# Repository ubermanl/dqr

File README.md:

# DqR Domo
DqR Domo permite el control, monitoreo y administración remota de su red eléctrica mediante cualquier dispositivo móvil o computadora personal.

Mediante DqR Domo podrá integrar y administrar de manera unificada todos sus dispositivos eléctricos, como luces, enchufes, portones, motores, etc., cualquiera sea su marca. La programación de tareas y la activación inteligente de dispositivos, junto con los reportes de consumo brindan toda la información que usted necesita para realizar un consumo más eficiente.

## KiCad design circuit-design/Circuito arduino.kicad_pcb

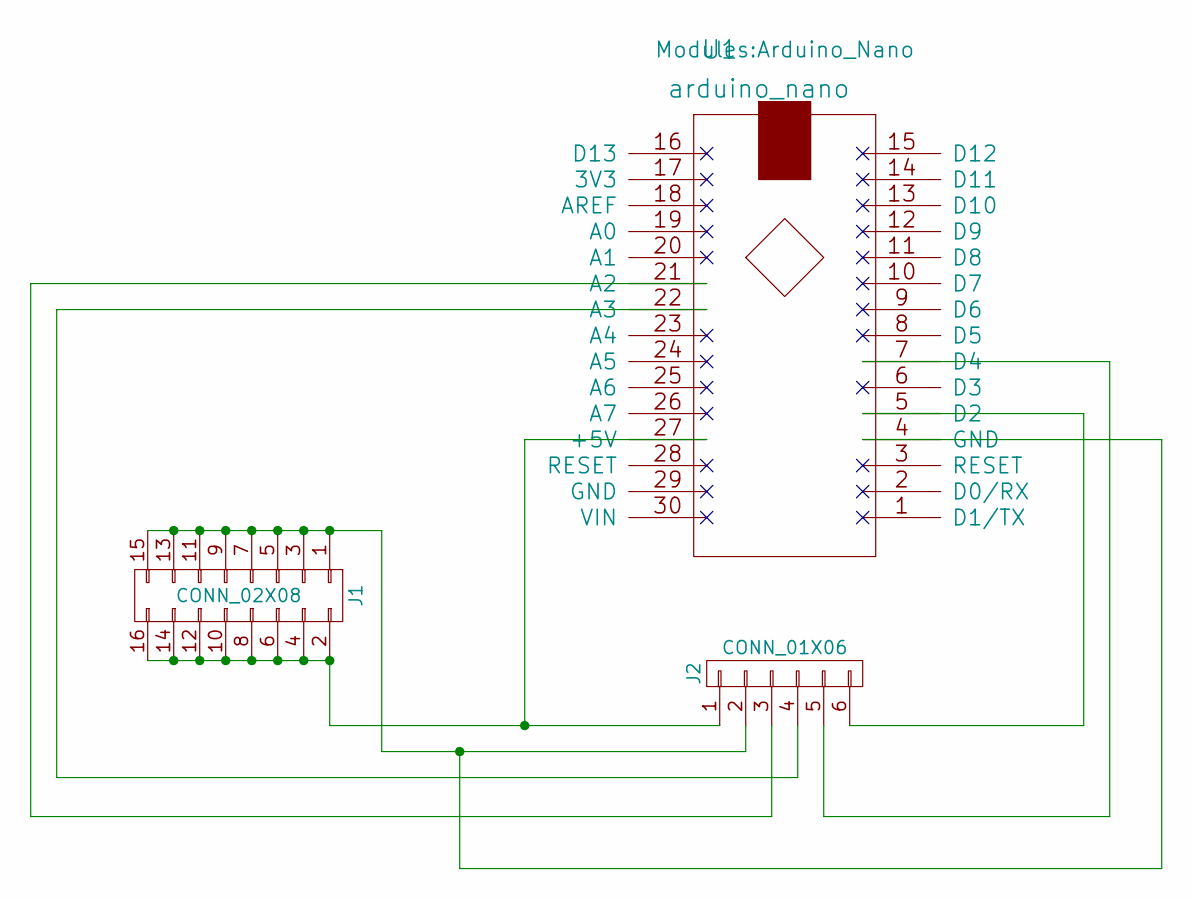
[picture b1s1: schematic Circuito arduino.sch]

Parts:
J1: CONN_02X08; Socket_Strip_Straight_2x08_Pitch2.54mm
J2: CONN_01X06; Pin_Header_Straight_1x06_Pitch2.54mm
U1: arduino_nano; Arduino_Nano

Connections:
unnamed: J1.1, J1.3, J1.5, J1.7, J1.9, J1.11, J1.13, J1.15, J2.2, U1.4 (GND)
unnamed: J1.2, J1.4, J1.6, J1.8, J1.10, J1.12, J1.14, J1.16, J2.1, U1.27 (+5V)
unnamed: J2.3, U1.21 (A2)
unnamed: J2.4, U1.22 (A3)
unnamed: J2.5, U1.7 (D4)
unnamed: J2.6, U1.5 (D2)

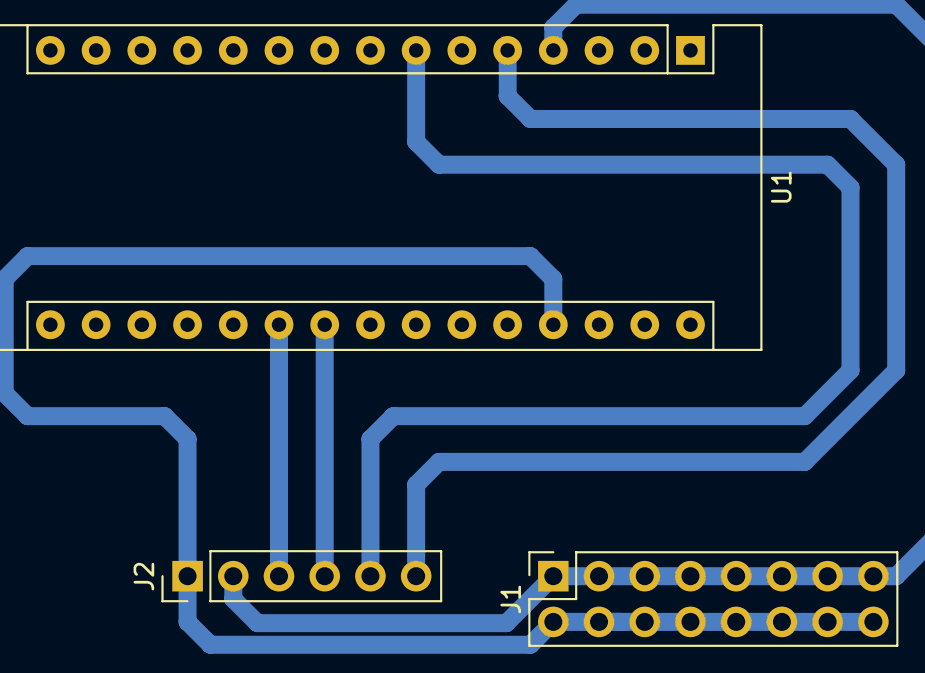
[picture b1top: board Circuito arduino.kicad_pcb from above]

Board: 2 copper layers, 3 parts (0 on the bottom side), 6 nets.

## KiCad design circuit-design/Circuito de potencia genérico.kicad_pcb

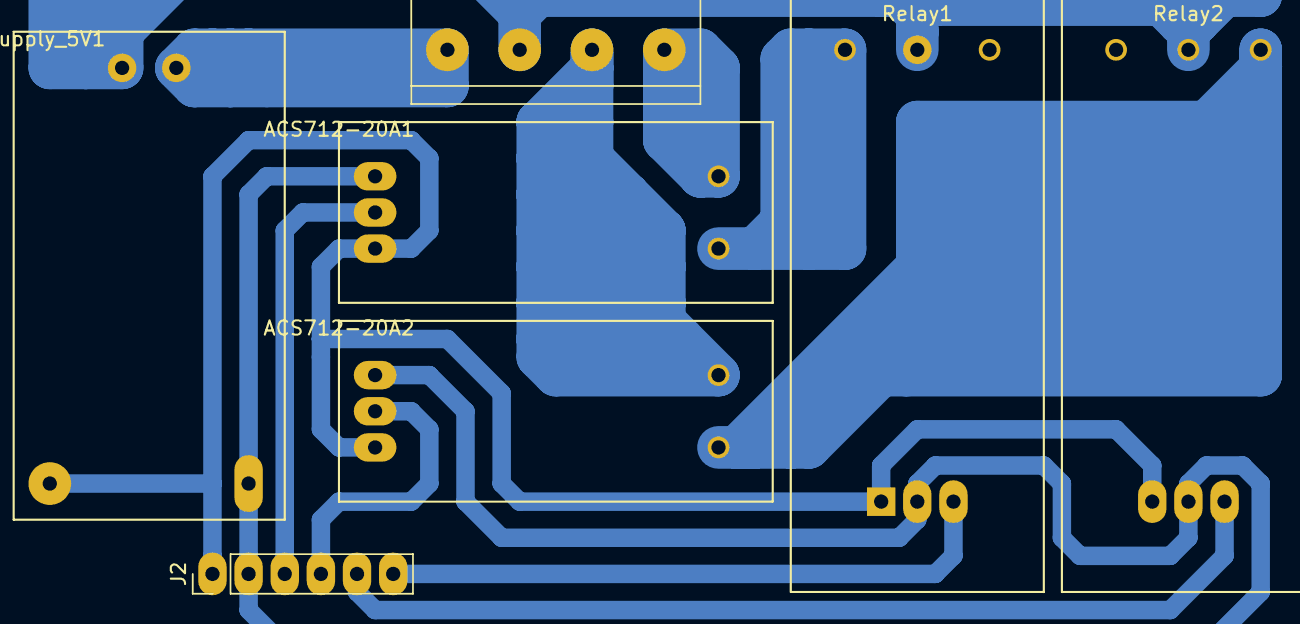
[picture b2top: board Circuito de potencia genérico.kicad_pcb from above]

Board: 2 copper layers, 7 parts (0 on the bottom side), 12 nets.

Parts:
ACS712-20A1, ACS712-20A2: ACS712-20A; ACS712
J1: Screw_Terminal_1x04; bornier4
J2: CONN_01X06; Pin_Header_Straight_1x06_Pitch2.54mm
PowerSupply_5V1: PowerSupply_5V; PowerSupply5V
Relay1, Relay2: Relay

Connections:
unnamed: ACS712-20A1.1, ACS712-20A2.1, J2.2, PowerSupply_5V1.4, Relay1.5, Relay2.5
unnamed: ACS712-20A1.2, J2.3
unnamed: ACS712-20A1.3, ACS712-20A2.3, J2.1, PowerSupply_5V1.3, Relay1.4, Relay2.4
unnamed: ACS712-20A1.4, J1.4
unnamed: ACS712-20A1.5, Relay1.2
unnamed: ACS712-20A2.2, J2.4
unnamed: ACS712-20A2.4, J1.3
unnamed: ACS712-20A2.5, Relay2.3
unnamed: J1.1, PowerSupply_5V1.2
unnamed: J1.2, PowerSupply_5V1.1, Relay1.1, Relay2.1
unnamed: J2.5, Relay2.6
unnamed: J2.6, Relay1.6

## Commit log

2017-04-02 Archivos iniciales para la prueba del dataset de UCI
2017-04-08 Nuevo ejemplo de RNA en un monoambiente y monousuario
2017-04-09 Incluyendo script para generar dataset y script para correr la RNA por cli
2017-04-13 Se reemplazó hora y minuto por minuto relativo del día
2017-04-17 ratio-console web
2017-04-17 gitignore
2017-04-17 fix database.yml
2017-04-17 Rename README.rdoc to README.md
2017-04-24 Nuevo servicio que corre la RNA y escucha consultas por medio de una API
2017-04-24 Nuevo doc en formato md
2017-04-24 Borrando doc mal formateado
2017-04-26 Ordenando los archivos
2017-04-27 Readme de RNA
2017-04-30 Actualizando para que todo use minutos relativos
2017-04-30 Actualización del README
2017-04-30 Más readme
2017-04-30 Typo
2017-05-03 Archivo de texto con versiones de módulos de pip
2017-05-16 Agregado de Arduino Lux
2017-05-22 Prueba del sensor ACS712 con suma de cuadrados
2017-05-25 random changes
2017-05-25 Agregada estabilizacion inicial del ACS712
2017-05-28 Actualizado completamente para poner los distintos tipos de dispositivo. Se agrego la cuenta para pasar de steps a Ampere.
2017-05-28 Se incluye lectura del sensor de luminosidad y su librería. Se reorganizaron los archivos.
2017-06-05 Funciones para los distintos sensores
2017-06-05 Empezando la definición de la librería DqR
2017-06-05 Mas modificaciones al prototipo de libreria
2017-06-05 sensor sonido en funcion
2017-06-05 Lux: se incorpora mensajes serial
2017-06-07 diseño modelo DB
2017-06-07 Migrado todo el código a clases
2017-06-09 Arreglada la cuenta de consumo AC
2017-06-12 Agregado de Interrupt por hw para switch touch
2017-06-12 Pruebas con FSM
2017-06-12 Agregado de lib FSM
2017-06-25 Versión inicial con el formato de clases device-module-sensor
2017-06-25 Cambios menores en los constructores
2017-06-26 Saqué "public" de la llamada de las clases heredadas
2017-06-26 reorganización del contenido
2017-06-26 dqr device sensor constructor
2017-06-26 rake task
2017-06-27 a better sample database config
2017-06-27 Se modifico la función addModules()
2017-06-29 Actualizaciones de hoy
2017-07-02 Actualización del ejemplo de clasificación para que tome al pir como una señal digital (0 y 1) en vez de continua.
2017-07-02 Nuevo ejemplo con regresión
2017-07-02 Actualizaciones varias
2017-07-02 Eliminado un checkpoint de jupyter-notebook
2017-07-04 Cambios de la sesión del lunes 3 de Julio
2017-07-08 # Agregado de librerías de comunicación RF24* de arduino # Ejemplos de arduino de FSM y RF24 # Implementacion inicial del Dispositivo (arduino/ejemplos/device-main)
2017-07-08 Correccion log estado 4 de prueba inicial device-main
2017-07-08 refactorizacion
2017-07-08 Creando la función getModuleStatus
2017-07-08 Se cambió getModuleStatus para que devuelva puntero a module_t
2017-07-10 # Cambios en pruebas de arduino main device # Agregado de pruebas de comunicacion con estructuras de datos para payload tipo I
2017-07-11 # Cambios en estructuras de datos de payload I
2017-07-12 Starbucks commit
2017-07-13 Starbucks session 2
2017-07-13 Cambio de low por high y viceversa
2017-07-13 Starbucks session #3
2017-07-14 # Cambios en dqr-device: - Agregado de sensores con punteros - Setup de device mediante struct constante en config - Modificaciones varias
2017-07-16 # Integración de dqr-device con FSM y RF24 # Versión inicial con envío de Informes de estado al Ratio completa. # Notificación al Ratio según parámetro de todos los módulos y sensores configurados. #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
2017-07-18 # Agregado de control de overflow del valor acumulado para el sensado
2017-07-26 # Versión inicial del módulo de comunicaciones del Ratio: ratioComm # Cambios en la instanciación de sensores, se elimina el id y se pasa a usar el type_id
2017-08-16 Agrego los archivos de diseño de circuito hechos con KiCad
2017-08-23 Archivos kicad de placa power
2017-08-30 fixes consola
2017-08-30 idea files
2017-09-05 nueva version de consola ratio
2017-09-05 Ratio SQL Dump
    Para poder crear la DB sin la App momentaneamente
2017-09-06 archivos omitidos
2017-09-06 # Cambios en la identificacion de modulos. El mod_id se autogenera
2017-09-06 Update README.md
    Actualiza las versiones de rails y ruby
2017-09-07 # Version inicial de modulo de comunicacion completo del Ratio
2017-09-10 Se agrega timestamp en LOG2
2017-09-10 Función antirebote en la captura del touch
2017-09-10 Faltaba poner timestamp en LOG
2017-09-10 Cambié el estado por default de LUX, para que no se prenda la luz cuando se inicializa el dispositivo
2017-09-10 Circuito de potencia genérico - v1.0
2017-09-10 Circuito Arduino Nano
2017-09-11 arreglos ratio communication
2017-09-11 arreglos en la compilacion via makefile en ratio communication
2017-09-11 Se agregan la comunicacion arduino-rpi para los mensajes S y A
2017-09-11 correcciones ratio-comm
2017-09-11 correccion en ratio-comm
2017-09-11 arreglos de version de scrypt y authlogic en gemfile
2017-09-11 agregado de retry de envios de mensajes a la mesh
2017-09-11 correcciones en max retries de envios
2017-09-11 correccion en el retry de envios de mensajes
2017-09-11 correcciones en la captura de sensado infinito.
2017-09-11 modificado retries desde el cliente
2017-09-12 Se movió el log de botón apretado dentro del comparador de tiempo
2017-09-13 correccion a la BOLUDEZ que hice en dqrMaster...
2017-09-13 correccion final del infinite en dqlMaster
2017-09-13 correccion de medicion de ACS en arduino
2017-09-13 Se cambio el estado por default de LUX
2017-09-14 correccion en el touch event del arduino para evitar bouncing y presiones minimas
2017-09-18 Cambios y correcciones en la logica de estados de los modulos.
2017-09-18 se agrega operacion con override al accionamiento remoto via ratio
2017-09-25 Added control of oldStatus on Lux to attempt control the errors detected during testing
2017-09-26 Added code to disable buffered output on stdout and stderr so that it's more service friendly
2017-09-27 Se crearon archivos de sistema para manejar los servicios relacionados con dqr, por ahora solo dqrMaster.
2017-09-27 new console status
2017-09-27 log perform
2017-09-27 fix activate deactivate
2017-09-27 fix send
2017-10-04 ajax toggles, new graphs
2017-10-04 fix toggle button
2017-10-04 fsm status override always
2017-10-12 devices, graficos, responsive
2017-10-17 github #4, #5
2017-10-17 timestamps correction to UTC
2017-10-17 autorefresh
2017-10-18 # Agregado de ejemplo de sensor de temperatura
2017-10-19 fixes
2017-10-20 generate lux task@
2017-10-21 Agregado de sensor de temperatura y estructura de templates para arduino
2017-10-22 Added systemd startup scripts for ratioConsole and moved all OS files to own directory
2017-10-22 Updated ratioConsole dependency
2017-10-22 Adding files to load firewall on boot and save on reboot/shutdwon
2017-10-22 Adding syslog file for ratioConsole, and other minor tweaks
2017-10-23 Correcicon include de DHT en arduino
2017-10-23 graph units added, console preferences
2017-10-23 rake task for unit update
2017-10-23 lux unit replaced
2017-10-23 fix potentia units
2017-10-23 ui face lift
2017-10-24 Updating service dependencies so that they start in the appropriate order (there were sql unavailable errors)
2017-10-24 Agregado de desactivacion de Omni en Arduino. Se vuelve atras el maximo de sensores a 5.
2017-10-25 Se cambiaron los permisos por default de dqrSender al ser instalado, para que el usuario pi (rails) pueda ejecutarlo.
2017-10-30 Agregada la generación de dataset para todo el año 2017.
2017-10-30 Se incluye función para sensar sonido en dBs, y se modificó el sensado de temperatura para truncar después del primer decimal
2017-10-30 Correcciones menores en los comentarios
2017-10-30 schedules
2017-10-30 Agregado consumo de luz al dataset simulado.
2017-10-31 scheduled tasks
2017-10-31 rake task disabled
2017-11-01 Agregada simulación de consumo de la heladera
2017-11-01 Agregado de carga de dataset en la base de datos
2017-11-01 timeline
2017-11-02 Updated Formula to calculate dBs and set new reference values
2017-11-03 Se agrega luminosidad medida por el lux
2017-11-03 Corrección en generador de dataset y agregado de pruebas de Classifier2 con variables modificadas
2017-11-03 Agregada prueba de nuevas variables del classifier2
2017-11-03 Agregado de nuevo modelo para predecir cambios de estado del lux.
2017-11-03 Correcciones en modelos de Classifier2
2017-11-03 Se elimina el dataset del git ya que puede generarse a demanda.
2017-11-04 cambio minimo al generador
2017-11-06 scheduler phase 1
2017-11-08 Added rnaEngine service
2017-11-08 pinned devices, discovery, device names
2017-11-08 Cleanup and and gitignore for the jupyter notebook checkpoints
2017-11-09 print last sensed value
2017-11-10 Carga de simulación en tablas device_events y device_event_sensors en la base de datos de DWH.
2017-11-10 device event sensors index
2017-11-11 Modificaciones menores para Python 3
2017-11-11 Borrado de checkpoints
2017-11-12 Ejemplo basado en LSTM
2017-11-12 Modificaciones menores
2017-11-14 Agregado ETL para pasar de TRX a DWH y predicción de consumo por módulo.
2017-11-14 Completada la carga en DWH en el ETL de aed_bi
2017-11-15 schedules preview, fixes github#74 schedule deletion
2017-11-15 schedules include attribute
2017-11-15 wait message for all ajax
2017-11-15 schedules bug out of sync
2017-11-15 Ya ni me acuerdo que agregué acá
2017-11-16 statistics on dashboard
2017-11-16 Agregado de variable en classifier2
2017-11-16 Nuevos ejemplos Classifier y Classifier LSTM con normalización
2017-11-18 Added multithreading to rnaEngine
2017-11-19 Cambio de librería DHT para el sensor de temperatura.
2017-11-19 fixes schedule status not reflexed, dqrSender failed message
2017-11-19 Added method to check if a give module has a model trained
2017-11-19 Added method to check if a give module has a trained model
2017-11-19 Deleting old file not longer in use
2017-11-19 swagger endpoint class
2017-11-19 protection against user entry
2017-11-20 Arreglado el comportamiento ante módulos invalidos o inexistentes
2017-11-20 user experience unified, login enabled
2017-11-20 user password change
2017-11-20 Corrección de bug de sensado de dispositivos no Omni en arduino
2017-11-20 fixes status transition
2017-11-20 fixes status output
2017-11-20 Fixed state training model
2017-11-20 graphics with fixed scale
2017-11-20 scheduler enabled
2017-11-20 Added default view of rnaEngine on root to display available methods
2017-11-21 fixes schedules
2017-11-22 scheduler enabled/disabled
2017-11-22 previous status check on schedule stop
2017-11-22 previous state fixed
2017-11-22 check schedule module multiple inclusion
2017-11-22 positive inclusion message
2017-11-22 fixed selecting schedule outside visible area
2017-11-22 Primera version del dashboard y agregado de procesos para Base de Datos.
2017-11-22 Adding more methods to the rnaEngine API portal
2017-11-22 name uniqueness
2017-11-22 redirect to detect device
2017-11-22 longitud nombre ambiente
2017-11-22 max name length 30 for all
2017-11-24 Version 1.1 del dashboard
2017-11-26 RBAC simple
2017-11-26 web page title
2017-11-28 fixes users, enable schedules again
2017-11-29 github #93
2017-11-29 fixes security issue on devices
2017-11-29 reenable scheduler
2017-11-29 sensor types and graph scale
2017-11-29 restrict type id change on sensor
2017-11-29 redirect to sensor_types on delete rejected
2017-12-07 Enabled schedules
2017-12-11 Added template for devices with single potentia module
2017-12-11 Added initial readme
2017-12-11 Minor modification to readme
2017-12-14 Creado un nuevo modelo para mostrar en la presentación
2017-12-15 Sacando LIGHT_1m del modelo de predicción
